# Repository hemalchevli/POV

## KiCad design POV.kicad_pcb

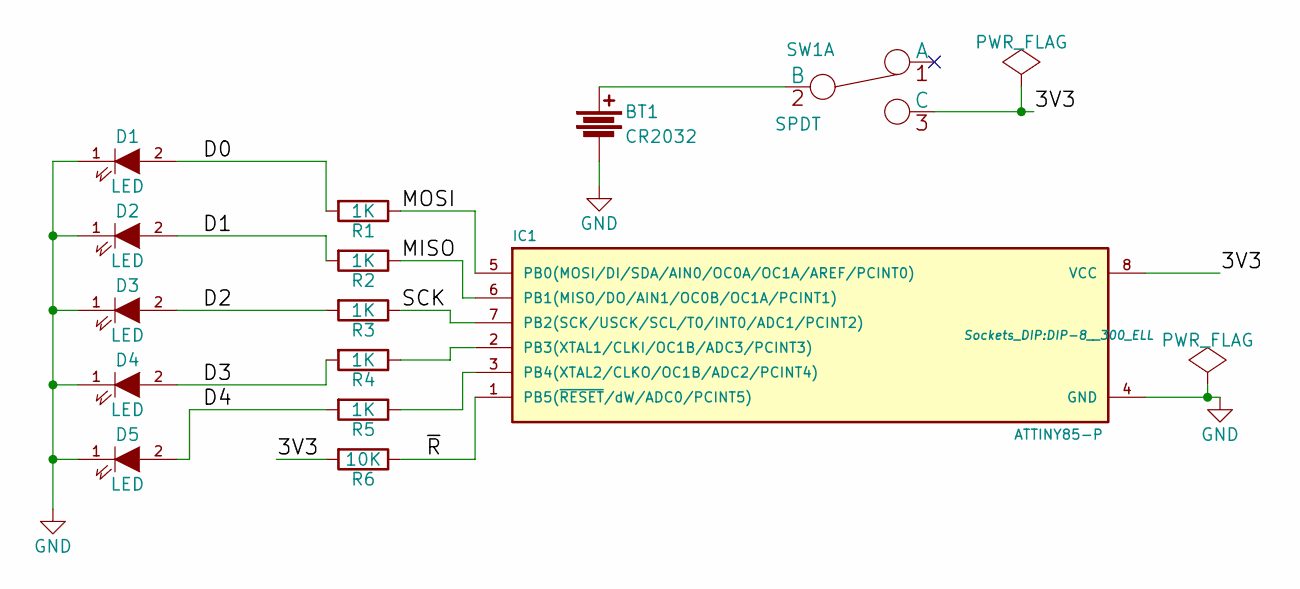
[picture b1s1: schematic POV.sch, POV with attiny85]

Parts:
BT1: CR2032
D1, D2, D3, D4, D5: LED; LED-5MM
IC1: ATTINY85-P; DIP-8__300_ELL
R1, R2, R3, R4, R5: 1K; Resistor_Vertical_RM5mm
R6: 10K; Resistor_Horizontal_RM10mm
SW1: SPDT; SW_Micro_SPST

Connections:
/3V3: IC1.8 (VCC), R6.2, SW1.3 (C)
/D0: D1.2 (A), R1.2
/D1: D2.2 (A), R2.2
/D2: D3.2 (A), R3.2
/D3: D4.2 (A), R4.2
/D4: D5.2 (A), R5.2
/MISO: IC1.6 (PB1(MISO/DO/AIN1/OC0B/OC1A/PCINT1)), R2.1
/MOSI: IC1.5 (PB0(MOSI/DI/SDA/AIN0/OC0A/OC1A/AREF/PCI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), R1.1
/SCK: IC1.7 (PB2(SCK/USCK/SCL/T0/INT0/ADC1/PCINT2)), R3.1
/~R: IC1.1 (PB5(~RESET~/dW/ADC0/PCINT5)), R6.1
GND: BT1.2, D1.1 (K), D2.1 (K), D3.1 (K), D4.1 (K), D5.1 (K), IC1.4 (GND)
unnamed: BT1.1, SW1.2 (B)
unnamed: IC1.2 (PB3(XTAL1/CLKI/OC1B/ADC3/PCINT3)), R4.1
unnamed: IC1.3 (PB4(XTAL2/CLKO/OC1B/ADC2/PCINT4)), R5.1

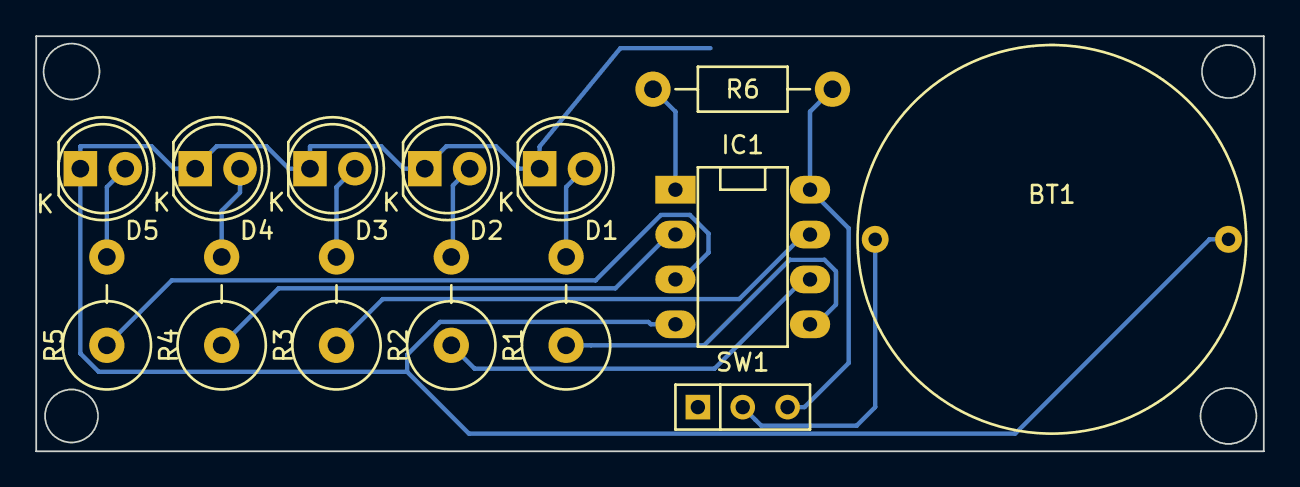
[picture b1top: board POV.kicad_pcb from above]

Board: 2 copper layers, 69.5 x 23.5 mm, 14 parts (0 on the bottom side), 14 nets.

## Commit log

2016-10-29 Added gerbers, updated FP,added logos
